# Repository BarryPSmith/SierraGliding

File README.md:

<h1 align=center>Sierra Gliding Weather</h1>

<p align=center>Low Interval Wind Station</p>

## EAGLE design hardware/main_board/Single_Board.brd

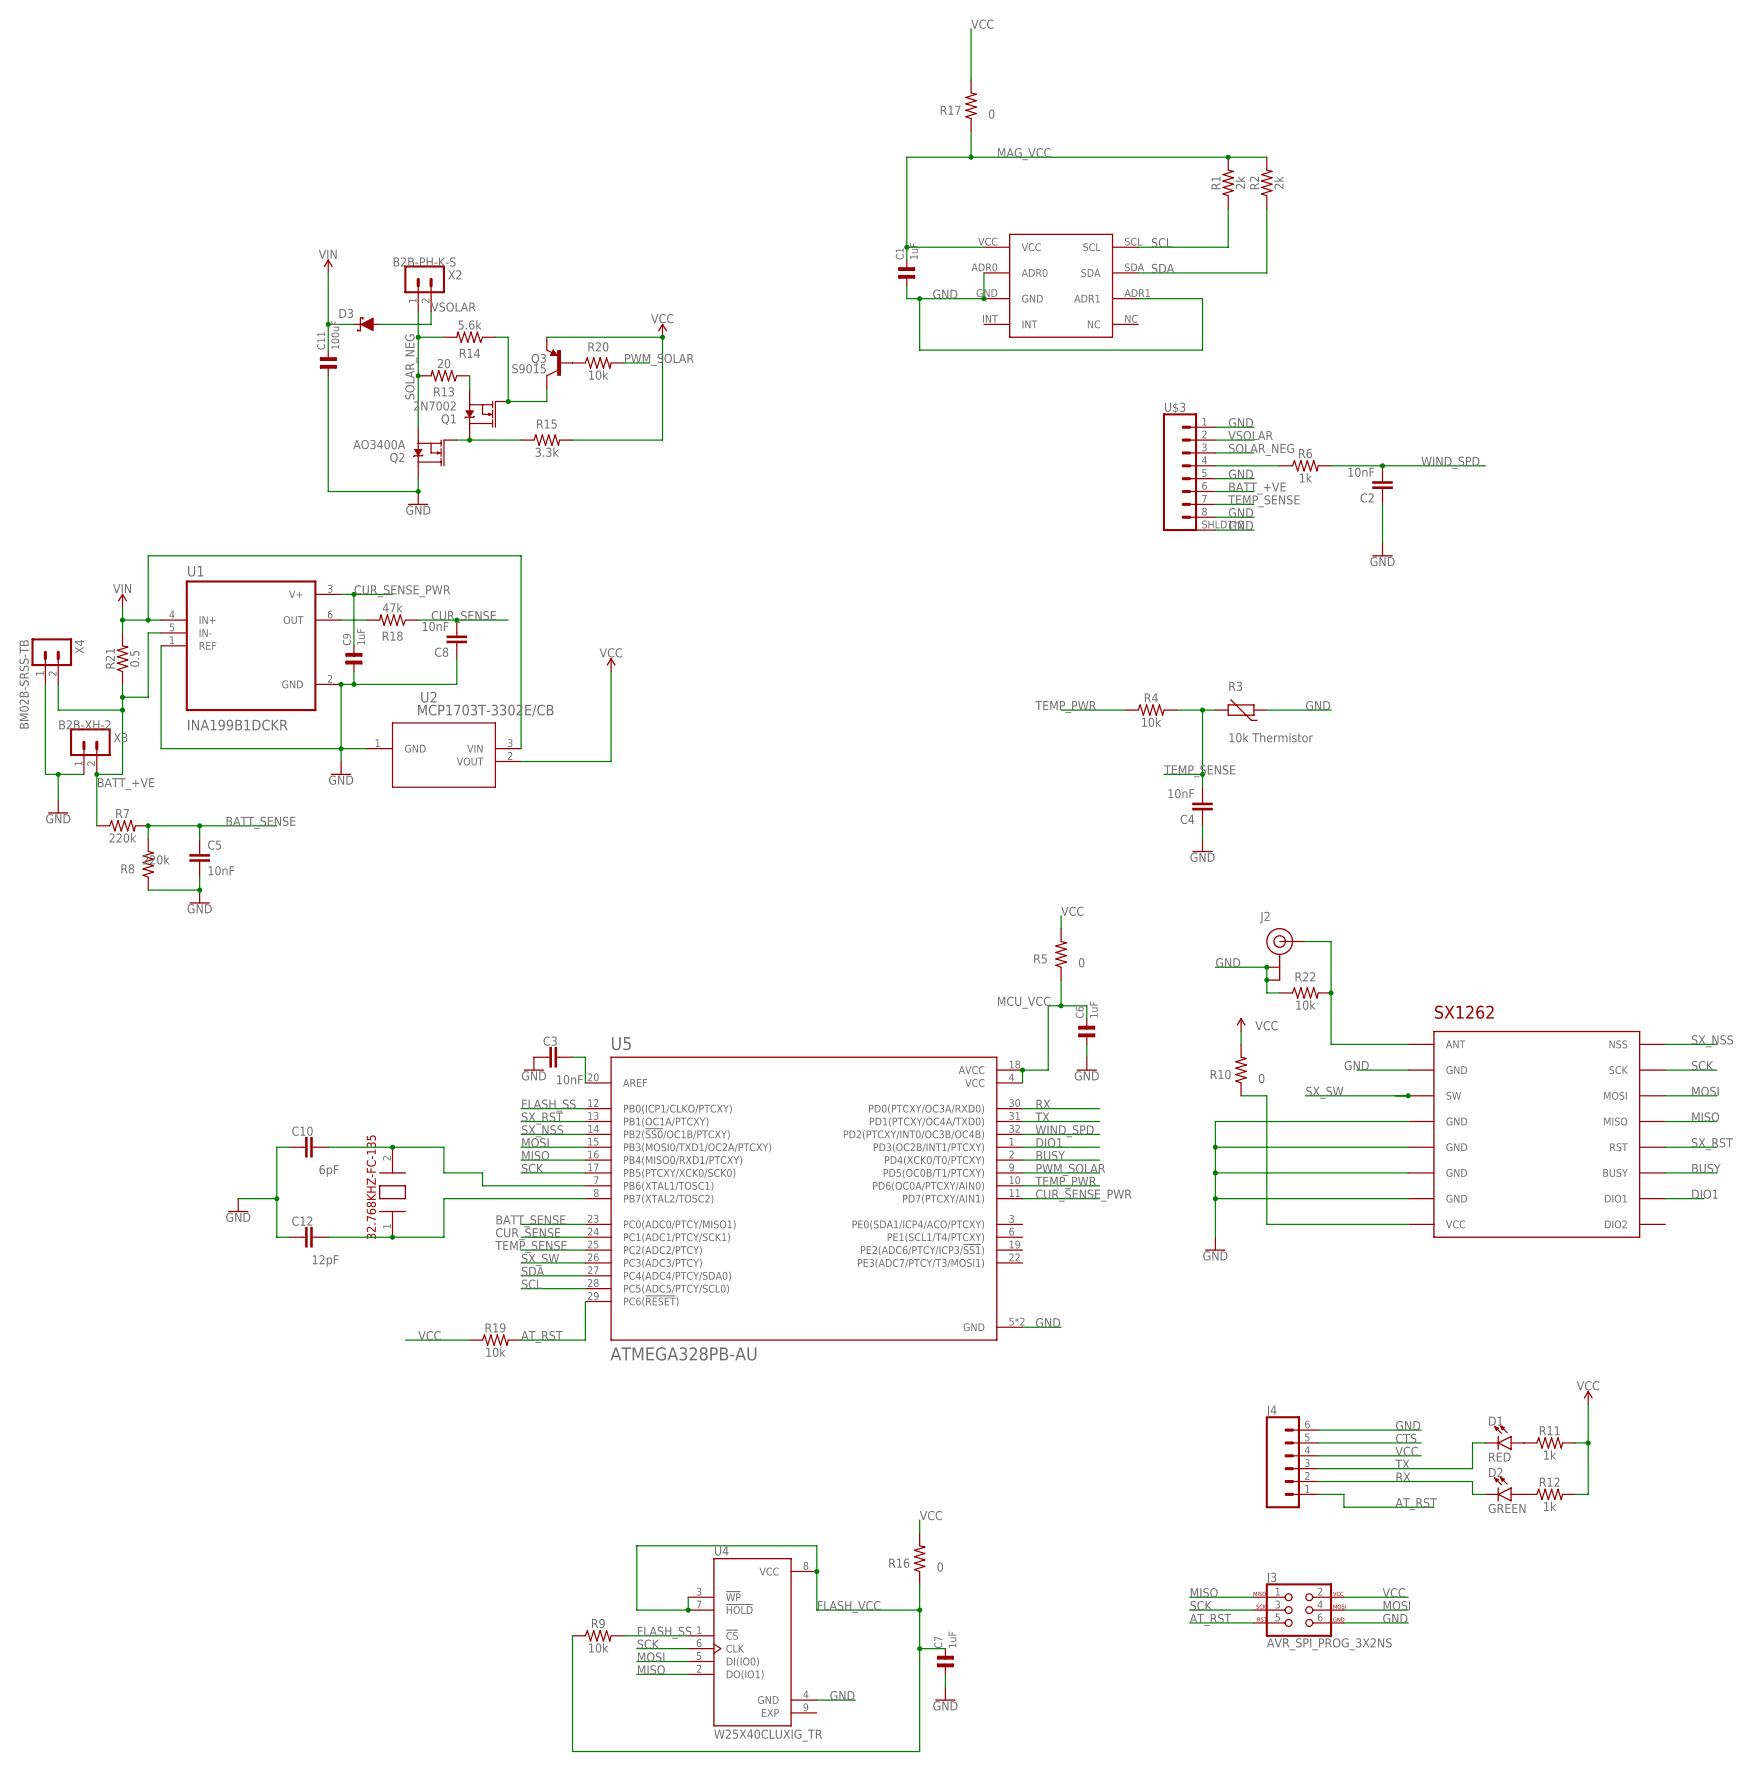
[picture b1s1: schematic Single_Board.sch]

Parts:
C1, C6, C7, C9: 1uF; 0805
C2, C3, C4, C5, C8: 10nF; 0603
C10: 6pF; 0603
C11: 100uF; 1206
C12: 12pF; 0603
D1: RED; LED-1206
D2: GREEN; LED-1206
D3: NSR0240HT1G; SOD-323
J2: U.FL
J3: AVR_SPI_PROG_3X2NS; 2X3-NS
J4: CONN_06NO_SILK_FEMALE_PTH; 1X06_NO_SILK
Q1: 2N7002; SOT23-3
Q2: AO3400A; SOT23-3
Q3: S9015; SOT23-3
R1, R2: 2k; 0805
R3: 10k Thermistor; R-5
R4, R9, R19, R20, R22: 10k; 0805
R5, R10, R16, R17: 0; 0805
R6, R11, R12: 1k; 0805
R7, R8: 220k; 0805
R13: 20; 0805
R14: 5.6k; 0805
R15: 3.3k; 0805
R18: 47k; 0805
R21: 0.5; 1206
U1: INA199B1DCKR; SOT65P210X110-6N
U2: MCP1703T-3302E/CB; SOT-23A_MC
U4: W25X40CLUXIG_TR; PSON50P300X200X60-9N
U5: ATMEGA328PB-AU; QFP80P900X900X120-32N
U$1: ALS31313; ALS31313-500
U$2: SX1262
U$3: RJSHE3380; RJHSE-3380
X1: 32.768KHZ-FC-135
X2: B2B-PH-K-S
X3: B2B-XH-2; B2B-XH-A
X4: BM02B-SRSS-TB

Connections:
ANT: J2.FEED (SIGNAL), R22.2, U$2.ANT
AT_RST: J3.5, J4.1, R19.2, U5.29 (PC6(!RESET!))
BATT_+VE: R7.1, R21.1, U1.5 (IN-), U$3.6, X3.2, X4.2
BATT_SENSE: C5.1, R7.2, R8.2, U5.23 (PC0(ADC0/PTCY/MISO1))
BUSY: U5.2 (PD4(XCK0/T0/PTCXY)), U$2.BUSY
CTS: J4.5
CUR_SENSE: C8.2, R18.1, U5.24 (PC1(ADC1/PTCY/SCK1))
CUR_SENSE_PWR: C9.2, U1.3 (V+), U5.11 (PD7(PTCXY/AIN1))
DIO1: U5.1 (PD3(OC2B/INT1/PTCXY)), U$2.DIO1
EXP: U4.9 (EXP)
FLASH_SS: R9.2, U4.1 (!CS), U5.12 (PB0(ICP1/CLKO/PTCXY))
FLASH_VCC: C7.2, R9.1, R16.1, U4.3 (!WP), U4.7 (!HOLD), U4.8 (VCC)
GND: C1.1, C2.1, C3.1, C4.1, C5.2, C6.1, C7.1, C8.1, C9.1, C10.1, C11.1, C12.1, J2.1 (GND), J2.2 (GND), J3.6, J4.6, Q2.3 (D), R3.1, R8.1, R22.1, U1.1 (REF), U1.2 (GND), U2.1 (GND), U4.4 (GND), U5.5 (GND), U5.21 (GND), U$1.ADR0, U$1.ADR1, U$1.GND, U$2.GND@1 (GND), U$2.GND@2 (GND), U$2.GND@3 (GND), U$2.GND@4 (GND), U$2.GND@5 (GND), U$3.1, U$3.5, U$3.8, U$3.SHLD1 (SHLD), U$3.SHLD2 (SHLD), X3.1, X4.1
MAG_VCC: C1.2, R1.2, R2.2, R17.1, U$1.VCC
MCU_VCC: C6.2, R5.1, U5.4 (VCC), U5.18 (AVCC)
MISO: J3.1, U4.2 (DO(IO1)), U5.16 (PB4(MISO0/RXD1/PTCXY)), U$2.MISO
MOSI: J3.4, U4.5 (DI(IO0)), U5.15 (PB3(MOSI0/TXD1/OC2A/PTCXY)), U$2.MOSI
unnamed: R10.1, U$2.VCC
unnamed: C3.2, U5.20 (AREF)
unnamed: Q1.2 (S), R13.1
unnamed: D1.A, R11.1
unnamed: R18.2, U1.6 (OUT)
unnamed: D2.A, R12.1
unnamed: C10.2, U5.7 (PB6(XTAL1/TOSC1)), X1.2 (2.XIN)
unnamed: C12.2, U5.8 (PB7(XTAL2/TOSC2)), X1.1 (1.XIN)
unnamed: Q3.1 (B), R20.1
unnamed: Q1.3 (D), Q2.1 (G), R15.1
unnamed: Q1.1 (G), Q3.3 (C), R14.1
unnamed: R6.1, U$3.4
PWM_SOLAR: R20.2, U5.9 (PD5(OC0B/T1/PTCXY))
RX: D2.C, J4.2, U5.30 (PD0(PTCXY/OC3A/RXD0))
SCK: J3.3, U4.6 (CLK), U5.17 (PB5(PTCXY/XCK0/SCK0)), U$2.SCK
SCL: R1.1, U5.28 (PC5(ADC5/PTCY/SCL0)), U$1.SCL
SDA: R2.1, U5.27 (PC4(ADC4/PTCY/SDA0)), U$1.SDA
SOLAR_NEG: Q2.2 (S), R13.2, R14.2, U$3.3, X2.1
SX_NSS: U5.14 (PB2(!SS0!/OC1B/PTCXY)), U$2.NSS
SX_RST: U5.13 (PB1(OC1A/PTCXY)), U$2.RST
SX_SW: U5.26 (PC3(ADC3/PTCY)), U$2.SW
TEMP_PWR: R4.1, U5.10 (PD6(OC0A/PTCXY/AIN0))
TEMP_SENSE: C4.2, R3.2, R4.2, U5.25 (PC2(ADC2/PTCY)), U$3.7
TX: D1.C, J4.3, U5.31 (PD1(PTCXY/OC4A/TXD0))
VCC: J3.2, J4.4, Q3.2 (E), R5.2, R10.2, R11.2, R12.2, R15.2, R16.2, R17.2, R19.1, U2.2 (VOUT)
VIN: C11.2, D3.C, R21.2, U1.4 (IN+), U2.3 (VIN)
VSOLAR: D3.A, U$3.2, X2.2
WIND_SPD: C2.2, R6.2, U5.32 (PD2(PTCXY/INT0/OC3B/OC4B))

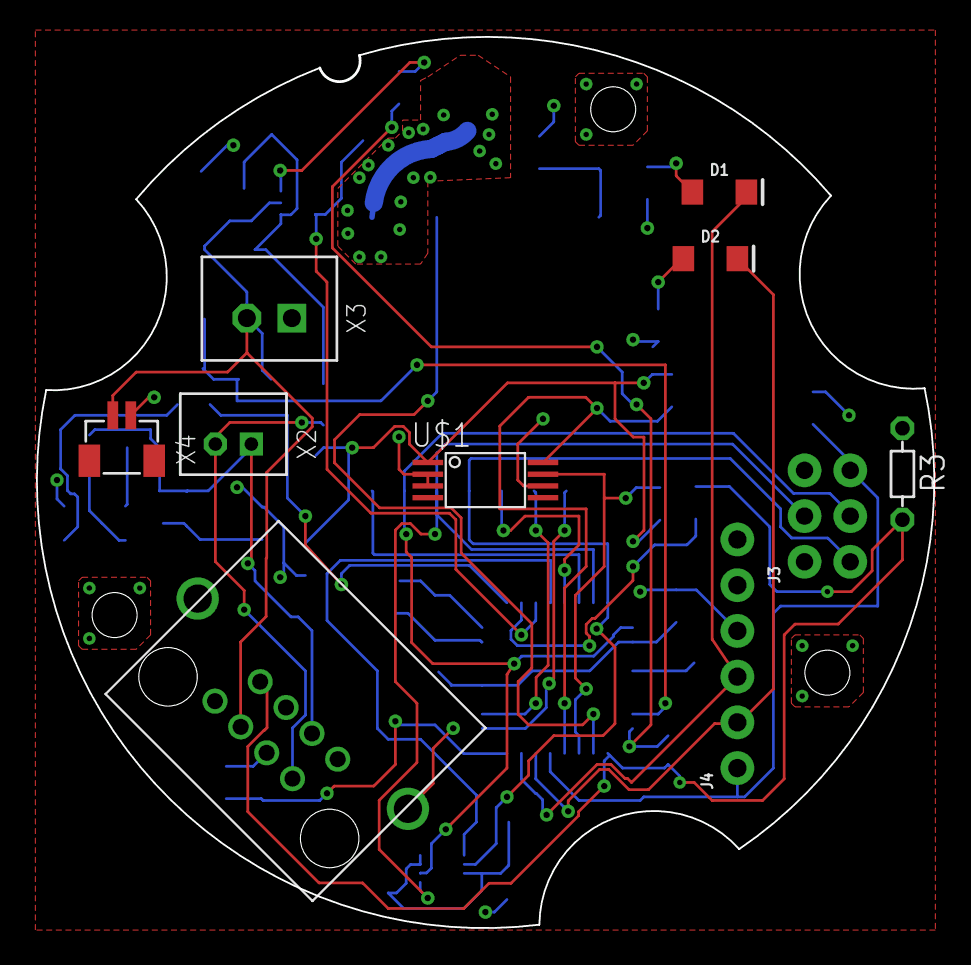
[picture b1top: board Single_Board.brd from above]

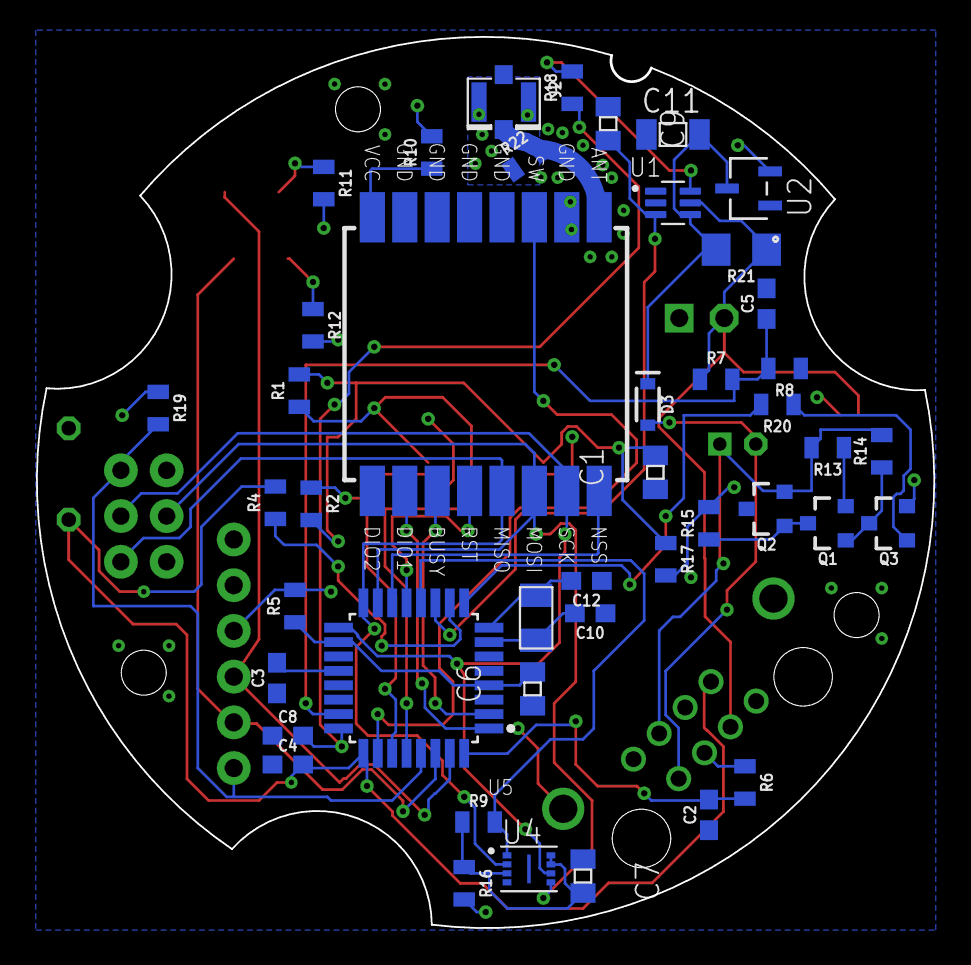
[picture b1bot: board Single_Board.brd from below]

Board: 2 copper layers, 49.8 x 49.5 mm, 54 parts (44 on the bottom side), 43 nets.

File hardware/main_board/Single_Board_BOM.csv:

Qty,Designator,Comment,Package,Device,LCSC Part #,Description
4,"R5, R10, R16, R17",0,805,RESISTOR0805,C17477,Generic Resistor Package
1,R21,0.5,1206,RESISTOR1206,C25340,Generic Resistor Package
1,D3,NSR0240HT1G,SOD-323,DIODE-SCHOTTKY,C152519,Schottky diode
1,C11,100uF,1206,C1206,C15008,Ceramic capacitor
4,"R4, R9, R19, R20",10k,805,RESISTOR0805,C17414,Generic Resistor Package
5,"C2, C3, C4, C5, C8",10nF,603,10NF-0603-50V-10%,C57112,Ceramic capacitor
3,"R6, R11, R12",1k,805,RESISTOR0805,C17513,Generic Resistor Package
4,"C1, C6, C7, C9",1uF,805,C0805,C28323,Generic Resistor Package
1,R13,20,805,RESISTOR0805,C17544,Generic Resistor Package
2,"R7, R8",220k,805,RESISTOR0805,C17556,Generic Resistor Package
1,Q1,2N7002,SOT23-3,MOSFET-NCH,C8545,N-channel MOSFETs
2,"R1, R2",2k,805,RESISTOR0805,C17604,Generic Resistor Package
1,X1,32.768KHZ-FC-135,32.768KHZ-FC-135,32.768KHZ-FC-135,C32346,RTC Crystal
1,R18,47k,805,RESISTOR0805,C17713,Generic Resistor Package
1,R14,5.6k,805,RESISTOR0805,C4382,Generic Resistor Package
1,Q2,AO3400A,SOT23-3,MOSFET-NCH,C20917,N-channel MOSFETs
1,U5,ATMEGA328P-AU,QFP80P900X900X120-32N,ATMEGA328P-AU,C14877,ATmega Series 20 MHz 32 KB Flash 2 KB SRAM 8-Bit Microcontroller - TQFP-32
1,U1,INA199B1DCKR,SOT65P210X110-6N,INA199B1DCKR,C398920,Current sense amplifier
1,U2,MCP1703T-3302E/CB,SOT-23A_MC,MCP1703T-3302E/CB,C53352,3.3V low power linear regulator
1,U4,W25X40CLUXIG_TR,PSON50P300X200X60-9N,W25X40CLUXIG_TR,C401661,4Mb SPI flash
1,C10,6pF,603,C0603,C37474,Ceramic capacitor
1,C12,12pF,603,C0603,C38523,Ceramic capacitor
1,R15,3.3k,805,RESISTOR0805,C26010,Generic Resistor Package
1,Q3,S9015,SOT23-3,TRANS_PNP,C2149,PNP transistor

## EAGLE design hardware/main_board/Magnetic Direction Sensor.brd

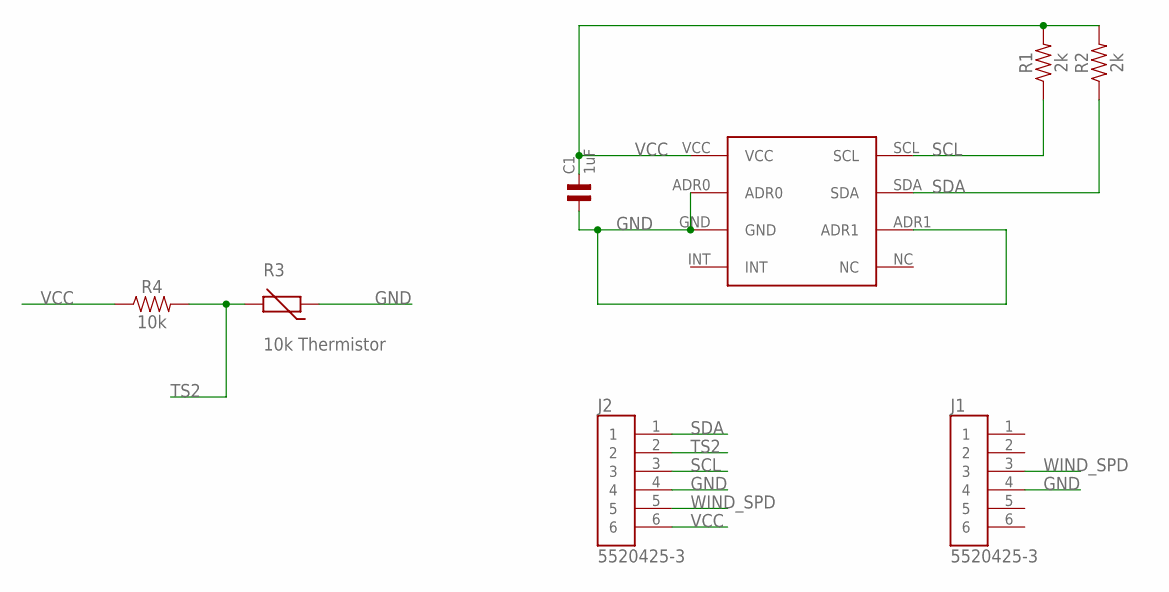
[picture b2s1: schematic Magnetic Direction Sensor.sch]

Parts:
C1: 1uF; 0805
J1, J2: 5520425-3; TE_5520425-3
R1, R2: 2k; 0805
R3: 10k Thermistor; R-5
R4: 10k; 0805
U$1: ALS31313; ALS31313-500

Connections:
GND: C1.1, J1.4, J2.4, R3.1, U$1.ADR0, U$1.ADR1, U$1.GND
SCL: J2.3, R1.1, U$1.SCL
SDA: J2.1, R2.1, U$1.SDA
TS2: J2.2, R3.2, R4.2
VCC: C1.2, J2.6, R1.2, R2.2, R4.1, U$1.VCC
WIND_SPD: J1.3, J2.5

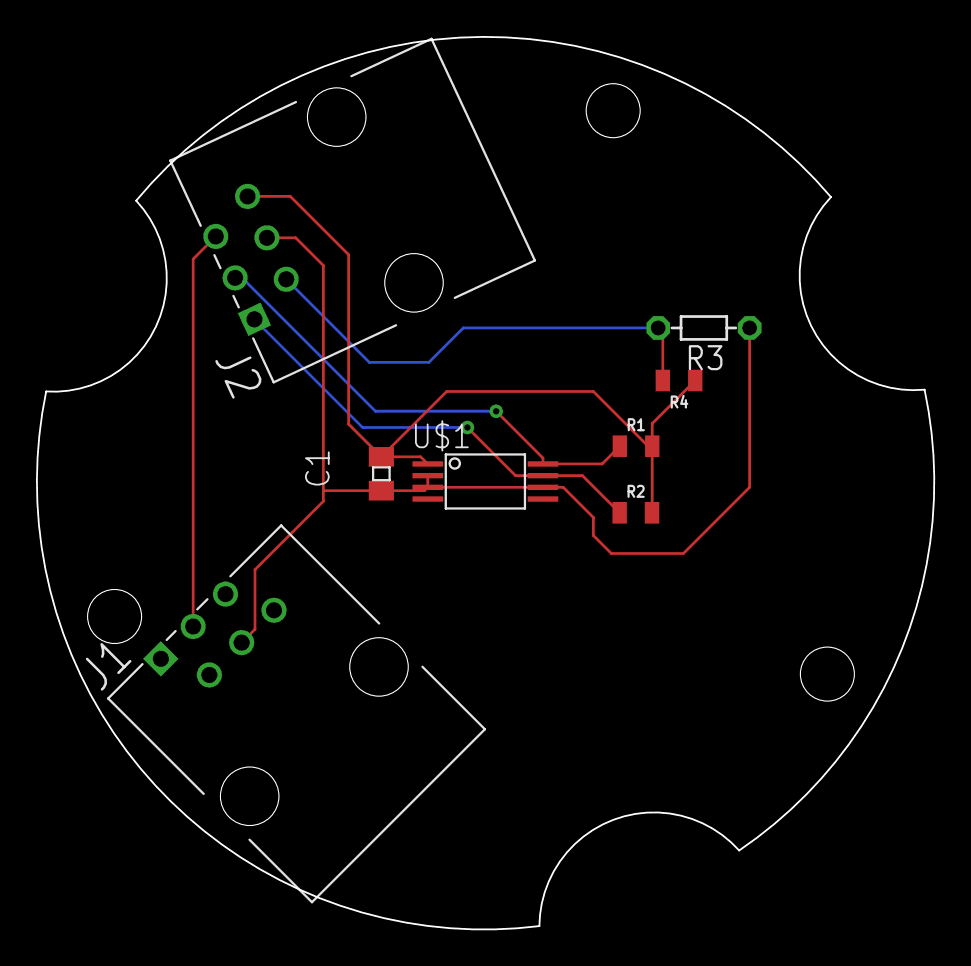
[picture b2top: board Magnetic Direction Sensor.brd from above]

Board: 2 copper layers, 49.9 x 49.6 mm, 8 parts (0 on the bottom side), 6 nets.

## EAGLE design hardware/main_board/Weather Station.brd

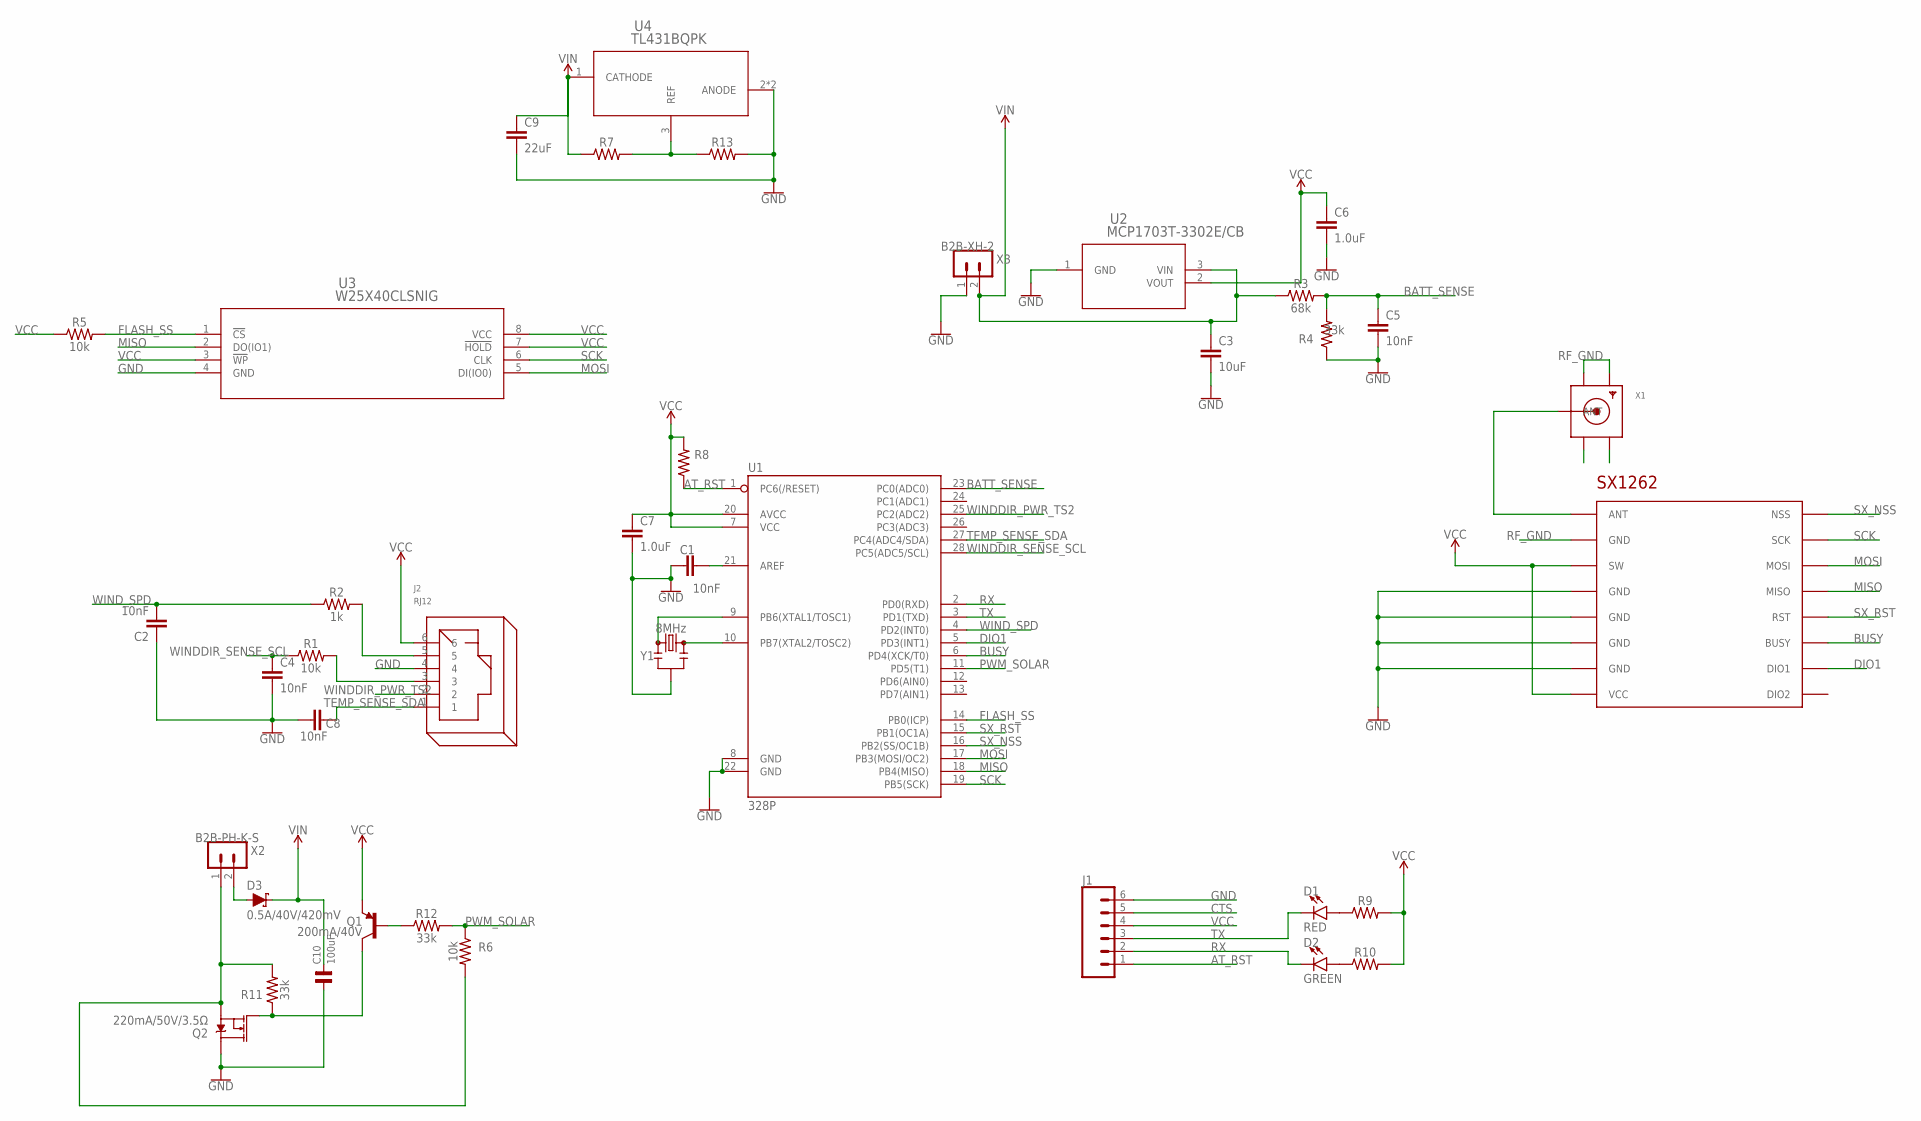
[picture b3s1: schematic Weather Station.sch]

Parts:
C1, C2, C4, C5, C8: 10nF; 0603
C3: 10uF; 0603
C6: 1.0uF; 0603
C7: 1.0uF; 0805
C9: 22uF; 0805
C10: 100uF; 1206
D1: RED; LED-1206
D2: GREEN; LED-1206
D3: 0.5A/40V/420mV; SOD-323
J1: CONN_06NO_SILK_FEMALE_PTH; 1X06_NO_SILK
J2: RJ12
Q1: 200mA/40V; SOT23-3
Q2: 220mA/50V/3.5Ω; SOT23-3
R1, R5, R6: 10k; 0805
R2: 1k; 0805
R3: 68k; 0805
R4, R11, R12: 33k; 0805
R7, R8, R9, R10, R13: 0805
U1: 328P; DIP28
U2: MCP1703T-3302E/CB; SOT-23A_MC
U3: W25X40CLSNIG; WIN_SN-8
U4: TL431BQPK; PK3
U$1: SX1262
X1: SMACONNECTOR_EDGE_UFL; SMA_EDGELAUNCH_UFL
X2: B2B-PH-K-S
X3: B2B-XH-2; B2B-XH-A
Y1: 8MHz; RESONATOR-SMD-3.2X1.3

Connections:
ANT: U$1.ANT, X1.P (ANT)
AT_RST: J1.1, R8.1, U1.1 (PC6(/RESET))
BATT_SENSE: C5.1, R3.2, R4.2, U1.23 (PC0(ADC0))
BUSY: U1.6 (PD4(XCK/T0)), U$1.BUSY
CTS: J1.5
DIO1: U1.5 (PD3(INT1)), U$1.DIO1
FLASH_SS: R5.2, U1.14 (PB0(ICP)), U3.1 (!CS)
GND: C1.1, C2.1, C3.2, C4.2, C5.2, C6.2, C7.2, C8.2, C9.2, C10.1, J1.6, J2.4, Q2.3 (D), R4.1, R13.2, U1.8 (GND), U1.22 (GND), U2.1 (GND), U3.4 (GND), U4.2 (ANODE), U4.A2 (ANODE), U$1.GND@2 (GND), U$1.GND@3 (GND), U$1.GND@4 (GND), U$1.GND@5 (GND), X3.1, Y1.2
MISO: U1.18 (PB4(MISO)), U3.2 (DO(IO1)), U$1.MISO
MOSI: U1.17 (PB3(MOSI/OC2)), U3.5 (DI(IO0)), U$1.MOSI
unnamed: R7.2, R13.1, U4.3 (REF)
unnamed: J2.5, R2.2
unnamed: D1.A, R9.1
unnamed: D2.A, R10.1
unnamed: J2.3, R1.2
unnamed: C1.2, U1.21 (AREF)
unnamed: Q2.2 (S), R6.2, R11.2, X2.1
unnamed: U1.9 (PB6(XTAL1/TOSC1)), Y1.1
unnamed: U1.10 (PB7(XTAL2/TOSC2)), Y1.3
unnamed: Q1.3 (C), Q2.1 (G), R11.1
unnamed: Q1.1 (B), R12.1
unnamed: D3.A, X2.2
PWM_SOLAR: R6.1, R12.2, U1.11 (PD5(T1))
RF_GND: U$1.GND@1 (GND), X1.GND@1 (GND1), X1.GND@2 (GND2)
RX: D2.C, J1.2, U1.2 (PD0(RXD))
SCK: U1.19 (PB5(SCK)), U3.6 (CLK), U$1.SCK
SX_NSS: U1.16 (PB2(SS/OC1B)), U$1.NSS
SX_RST: U1.15 (PB1(OC1A)), U$1.RST
TEMP_SENSE_SDA: C8.1, J2.1, U1.27 (PC4(ADC4/SDA))
TX: D1.C, J1.3, U1.3 (PD1(TXD))
VCC: C6.1, C7.1, J1.4, J2.6, Q1.2 (E), R5.1, R8.2, R9.2, R10.2, U1.7 (VCC), U1.20 (AVCC), U2.2 (VOUT), U3.3 (!WP), U3.7 (!HOLD), U3.8 (VCC), U$1.SW, U$1.VCC
VIN: C3.1, C9.1, C10.2, D3.C, R3.1, R7.1, U2.3 (VIN), U4.1 (CATHODE), X3.2
WINDDIR_PWR_TS2: J2.2, U1.25 (PC2(ADC2))
WINDDIR_SENSE_SCL: C4.1, R1.1, U1.28 (PC5(ADC5/SCL))
WIND_SPD: C2.2, R2.1, U1.4 (PD2(INT0))

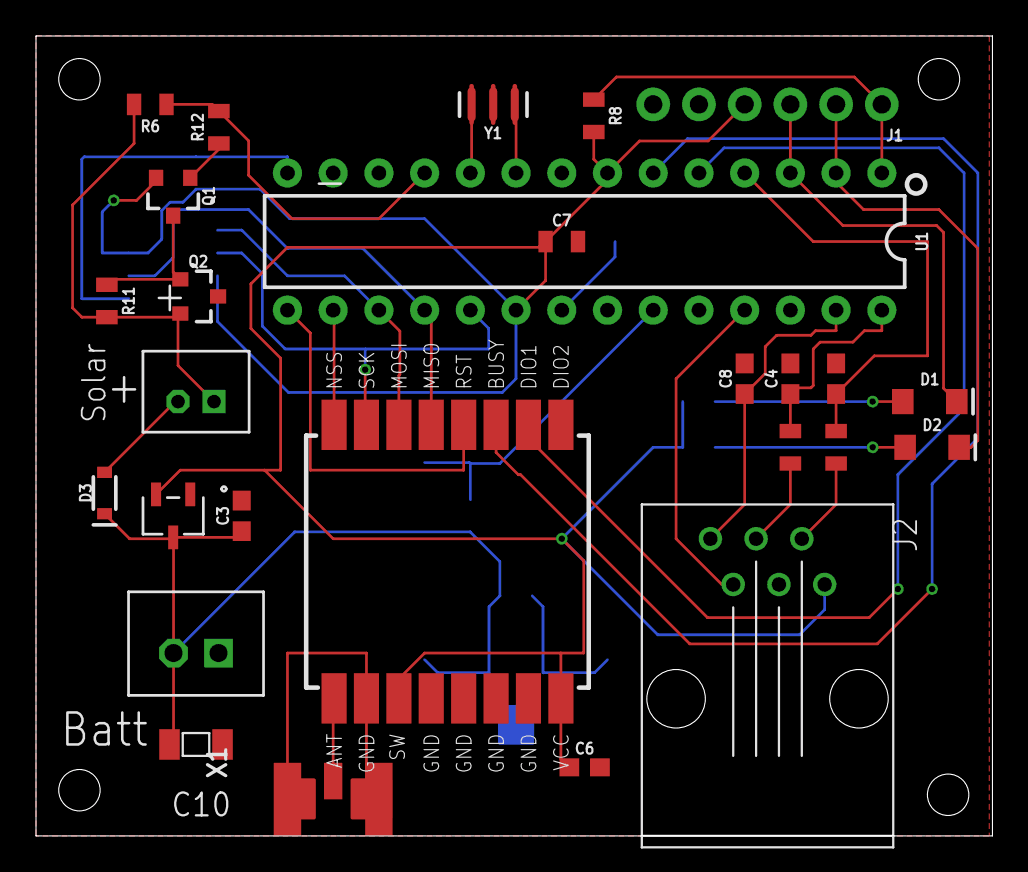
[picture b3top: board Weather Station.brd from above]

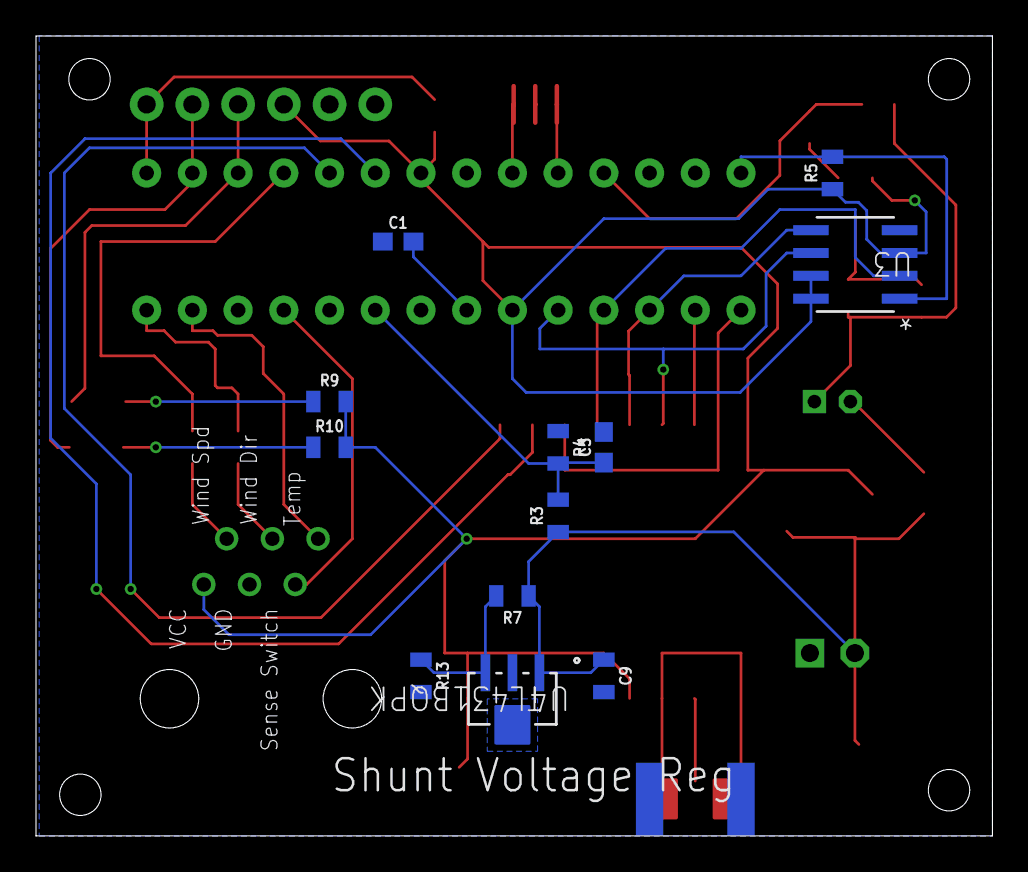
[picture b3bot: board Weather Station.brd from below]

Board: 2 copper layers, 53.1 x 44.4 mm, 39 parts (12 on the bottom side), 34 nets.

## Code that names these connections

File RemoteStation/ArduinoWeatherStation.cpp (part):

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#if SX_SWITCH != A3
  pinMode(A3, INPUT_PULLUP);
#endif
#if TEMP_PWR_PIN != 6
  pinMode(6, INPUT_PULLUP);
#endif
#if CURRENT_SENSE_PWR != 7
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void enterStasis()
{
  // If we don't have a wind speed pin, we can't enter stasis
#ifdef WIND_SPD_PIN
  batteryMode = BatteryMode::Stasis;
  WeatherProcessing::enterDeepSleep();
  sleepRadio();
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  static_assert(LED_ON == LOW);
  static_assert(LED_OFF == HIGH);
  auto delay2 = delay_ms / 4;
  PORTD &= ~(_BV(PD0) | _BV(PD1));
  //digitalWrite(LED_PIN0, LED_ON);
  //digitalWrite(LED_PIN1, LED_ON);
  delay(delay2);
  PORTD |= _BV(PD1);//digitalWrite(LED_PIN1, LED_OFF);
  delay(delay2);
  PORTD &= ~_BV(PD1); //digitalWrite(LED_PIN1, LED_ON);
  delay(delay2);
  PORTD |= _BV(PD1); //digitalWrite(LED_PIN1, LED_OFF);
  delay(delay2);
  //Shorten it to 11 bits (=-1024 to + 1023)
  for (byte i = 0; i < 11; i++)
  {
    if (i & 1)
      PORTD |= _BV(PD0); //OFF for i = 1, 3, 5, 7, 9, 11
    else
      PORTD &= ~_BV(PD0); //ON for i = 0, 2, 4, 8, 10
    //digitalWrite(LED_PIN0, (i & 1) ? LED_OFF : LED_ON);
    if (errorCode & 1)
      PORTD &= ~_BV(PD1);
    else
      PORTD |= _BV(PD1);
    //digitalWrite(LED_PIN1, (errorCode & 1) ? LED_ON : LED_OFF);
    errorCode = errorCode >> 1;
    delay(delay_ms);
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  //digitalWrite(LED_PIN0, LED_OFF);
  //digitalWrite(LED_PIN1, errorCode & (0x800 >> 11) ? LED_ON : LED_OFF);
  if (errorCode & (0x800 >> 11))
    PORTD &= ~_BV(PD1);
  else
    PORTD |= _BV(PD1);
  PORTD |= _BV(PD0);
  delay(delay_ms);
  signalOff();
#endif
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
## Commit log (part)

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2019-10-06 Allow switching between durations
2019-10-06 Add Error Handling
2019-10-06 Add windspeed legend checks
2019-10-06 Add clearfix
2019-10-06 Add actual lat/lngs
2019-10-07 Add sample URL param validity checks
2019-10-08 Fix README geojson
2019-10-08 Made dotNet_Receiver configurable. Added wind direction offset to database schema
2019-10-08 Separated wind and battery charts. Legend work.
2019-10-09 Ignore all sqlite files
2019-10-09 Chart time axes appear. Needed min and max on annotations.
2019-10-09 Made graphs take up all available space through use of custom grid styles.
2019-10-09 Fixed a bug in legend parsing while fetching stations. Unimportant since it's not used
2019-10-10 Secure websockets
2019-10-10 Migrated receiver to dotNet core 3.0 so it can run on Linux
2019-10-13 Receiver improvements
2019-10-17 Rearranged hardware folder. Adding more hardware documentation
2019-10-20 Added ability to pan graphs using click and drag. Things are strange. Why do I now need to require('Annotations')?
2019-10-20 Windspeed scaling after panning and loading new data
2019-11-05 Added an optional status message to stations
2019-11-14 Weather station LoRa work
2019-11-15 Work on the arduino software. Also an arduino Kiss Modem.
2019-11-16 Made everything work of Timer1 millis. Added debounce to windspeed logic.
2019-11-19 A bunch of changes. Most significantly, made the modem use DIO2 as a RF switch. Tried to add Moteino support with the RF96 module. No luck yet. Some other stuff
2019-11-20 Clawing memory back using F(...)
2019-11-28 Changed to Timer2 so we can put the ATMega to sleep
2019-12-10 Big changes all over.
2019-12-11 Customisable battery range. Switched erratic time behaviour when switching between battery and wind.
2019-12-24 Fixed a couple bugs in millis and micros implementations
2020-01-05 Changed to gnu make instead of NMAKE. Various other work too Untested.
2020-01-12 Added some power saving stuff, disabled for now. This image should be run at Flynns for a while
2020-01-25 Added temperature sense. MCU sleeps more.
2020-01-28 Added wind calibration. Started using namespaces. Added indicator LEDs
2020-01-28 Weather station + receiver stuff.
2020-02-03 Website work
2020-02-03 More Mt Tom fixes.
2020-02-10 Fixed a bug in weather relay. Made receiver more resilient to this bug.
2020-02-13 Reworked site to use webpack. Reworked server sampling to do it in SQLite for improved performance.
2020-02-14 Added capability to change wind direction graph centre.
2020-02-17 Remote Programming implemented (not connected). Tweaked relay logic.
2020-02-25 Webserver bugfix
2020-02-25 Minor code cleanup
2020-02-27 Changed site to 15 minute default duration
2020-03-03 Fixed legends not being visible until chart got new data
2020-03-09 Added transparency to wind direction chart
2020-03-14 Fix messed up arrow indicator on firefox
2020-03-14 Fix firefox
2020-03-14 Alignment
2020-03-21 Random ID assigment limited to [1,127] because IDs can't start with 0x80
2020-04-03 Clawed back some space
2020-04-06 Bump minimist from 1.2.0 to 1.2.3 in /web
    Bumps [minimist](https://github.com/substack/minimist) from 1.2.0 to 1.2.3.
    - [Release notes](https://github.com/substack/minimist/releases)
    - [Commits](https://github.com/substack/minimist/compare/1.2.0...1.2.3)
2020-04-09 ALS Wind direction bug fixes. Added ability to chain receivers using UDP. QueryVolatileResponse bugfix.
2020-04-14 Added more power saving options: Disable continuous receive & deep sleep, clock divider Receiver: Ability to handle extra bytes on weather packets
2020-05-01 Added magnetic direction sensor board
2020-05-03 Added windy poster.
2020-05-12 Station backward compatibility fixes. Site: Can now request hidden stations, made temperature chart sizeable on click.
2020-05-19 Added mechanism to write ALS eeprom
2020-05-23 More bugfixes with CSMA queueing Added GUIDs to UDP packets to avoid repeated processing
2020-05-31 Added docs folder
2020-05-31 Set theme jekyll-theme-slate
2020-06-24 Documentation work
2020-07-18 Bump lodash from 4.17.14 to 4.17.19 in /web/site
    Bumps [lodash](https://github.com/lodash/lodash) from 4.17.14 to 4.17.19.
    - [Release notes](https://github.com/lodash/lodash/releases)
    - [Commits](https://github.com/lodash/lodash/compare/4.17.14...4.17.19)
2020-08-08 Improved chart time axes, aligned detail charts with wind chart.
2020-08-31 Big changes: 2.3, flash message storage, permanent time
2020-09-03 More station improvements
2020-09-04 Added command guards. Saves stack trace on reboot.
2020-09-05 Programmer fixes with new extra CRC checks
2020-09-19 pany fix
2020-11-17 Added ability to jump times. Improved receiver command help
2020-12-08 Added daylight indicators
2020-12-08 Bump dot-prop from 4.2.0 to 4.2.1 in /web/site
    Bumps [dot-prop](https://github.com/sindresorhus/dot-prop) from 4.2.0 to 4.2.1.
    - [Release notes](https://github.com/sindresorhus/dot-prop/releases)
    - [Commits](https://github.com/sindresorhus/dot-prop/compare/v4.2.0...v4.2.1)
2021-01-01 Station improvements. Multi-subpacket handling in receiver. Out of order packets in site datamanager.
2021-02-01 Reduced web server load through low resolution tables
2021-02-02 Further sig fig reductions
2021-02-14 Saving program space: Removed many icalls Switched to home-brew synchronous two wire
2021-03-17 Removed remote switch control. Debug parameters changed.
2021-03-23 Found a problem where the solar PWM can latch closed. Temporary fix is to set an appropriate startup value that doesn't close it.
2021-04-04 Added old centroid file purely for history
2021-04-30 Bump ssri from 6.0.1 to 6.0.2 in /web/site
    Bumps [ssri](https://github.com/npm/ssri) from 6.0.1 to 6.0.2.
    - [Release notes](https://github.com/npm/ssri/releases)
    - [Changelog](https://github.com/npm/ssri/blob/v6.0.2/CHANGELOG.md)
    - [Commits](https://github.com/npm/ssri/compare/v6.0.1...v6.0.2)
2021-05-05 Added station groups
2021-05-10 Bump lodash from 4.17.20 to 4.17.21 in /web
    Bumps [lodash](https://github.com/lodash/lodash) from 4.17.20 to 4.17.21.
    - [Release notes](https://github.com/lodash/lodash/releases)
    - [Commits](https://github.com/lodash/lodash/compare/4.17.20...4.17.21)
2021-05-29 Bump ws from 7.1.2 to 7.4.6 in /web
    Bumps [ws](https://github.com/websockets/ws) from 7.1.2 to 7.4.6.
    - [Release notes](https://github.com/websockets/ws/releases)
    - [Commits](https://github.com/websockets/ws/compare/7.1.2...7.4.6)
2021-08-11 Bump path-parse from 1.0.6 to 1.0.7 in /web/site
    Bumps [path-parse](https://github.com/jbgutierrez/path-parse) from 1.0.6 to 1.0.7.
    - [Release notes](https://github.com/jbgutierrez/path-parse/releases)
    - [Commits](https://github.com/jbgutierrez/path-parse/commits/v1.0.7)
    ---
    updated-dependencies:
    - dependency-name: path-parse
2021-09-20 Bump color-string from 1.5.3 to 1.6.0 in /web/site
    Bumps [color-string](https://github.com/Qix-/color-string) from 1.5.3 to 1.6.0.
    - [Release notes](https://github.com/Qix-/color-string/releases)
    - [Changelog](https://github.com/Qix-/color-string/blob/master/CHANGELOG.md)
    - [Commits](https://github.com/Qix-/color-string/commits/1.6.0)
    ---
    updated-dependencies:
2021-11-01 Modem automatically restarts the radio if it doesn't receive a message in 6 seconds Stations select default frequency and bandwidth if frequency is out of range Fixed a bug with weather relay overflo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
2021-12-07 Added ability to change inbound preamble length
2021-12-08 Fixed a uninitalised pointer and threading bug introduced in previous commit.ISP programming now preserves EEPROM
2021-12-08 Re-enabled modem watchdog Inbound preamble length reset to 8 in low power modes Improved receiver logging
2021-12-11 Test function in receiver Debugging to try figure out what's going on with relays sometimes sending invalid data Misc formatting & display
2021-12-11 Improved gust calculation to use 4 rotations rather than 1. Webserver refuses packets with inverted windspeed / gust.
2021-12-14 The eternal struggle with memory. Fixed a bug where the current read packet could get corrupted when a packet is sent. Fixed a problem with buffer overrun when recording messages for relay Improved r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
2021-12-15 Got rid of npm security warnings, with some major version upgrades in there to boot.
2021-12-16 Add HTTPError
2021-12-16 npm audit really doesn't like sqlite5
2021-12-31 Added PWM to current display
2022-01-01 Receiver ability to handle RSSI/SNR on recently seen station list
2022-01-03 Limited preamble lengths to stop accidental bricking of stations. dotNetReceiver now configurable for stations with different version (instead of hardcoded.
2022-01-08 Fixed assignment to a constant variable error.
2022-01-21 Sunrise/sunset calcs now use actual station locations
2022-01-23 Button font size
2022-01-24 Re-enabled /all
2022-03-24 Bump minimist from 1.2.5 to 1.2.6 in /web/site
    Bumps [minimist](https://github.com/substack/minimist) from 1.2.5 to 1.2.6.
    - [Release notes](https://github.com/substack/minimist/releases)
    - [Commits](https://github.com/substack/minimist/compare/1.2.5...1.2.6)
    ---
    updated-dependencies:
    - dependency-name: minimist
2022-06-22 Bump Newtonsoft.Json in /dotNet_Receiver/dotNet_Receiver
    Bumps [Newtonsoft.Json](https://github.com/JamesNK/Newtonsoft.Json) from 12.0.3-beta2 to 13.0.1.
    - [Release notes](https://github.com/JamesNK/Newtonsoft.Json/releases)
    - [Commits](https://github.com/JamesNK/Newtonsoft.Json/commits/13.0.1)
    ---
    updated-dependencies:
    - dependency-name: Newtonsoft.Json
2022-11-13 Bump loader-utils from 1.4.0 to 1.4.2 in /web/site
    Bumps [loader-utils](https://github.com/webpack/loader-utils) from 1.4.0 to 1.4.2.
    - [Release notes](https://github.com/webpack/loader-utils/releases)
    - [Changelog](https://github.com/webpack/loader-utils/blob/v1.4.2/CHANGELOG.md)
    - [Commits](https://github.com/webpack/loader-utils/compare/v1.4.0...v1.4.2)
    ---
    updated-dependencies:
2022-12-08 Bump Newtonsoft.Json from 12.0.3 to 13.0.2 in /WindyPoster
    Bumps [Newtonsoft.Json](https://github.com/JamesNK/Newtonsoft.Json) from 12.0.3 to 13.0.2.
    - [Release notes](https://github.com/JamesNK/Newtonsoft.Json/releases)
    - [Commits](https://github.com/JamesNK/Newtonsoft.Json/compare/12.0.3...13.0.2)
    ---
    updated-dependencies:
    - dependency-name: Newtonsoft.Json
2023-01-07 Bump json5 from 1.0.1 to 1.0.2 in /web/site
    Bumps [json5](https://github.com/json5/json5) from 1.0.1 to 1.0.2.
    - [Release notes](https://github.com/json5/json5/releases)
    - [Changelog](https://github.com/json5/json5/blob/main/CHANGELOG.md)
    - [Commits](https://github.com/json5/json5/compare/v1.0.1...v1.0.2)
    ---
    updated-dependencies:
2023-05-04 Receiver stuff
2023-05-04 Fix lints
2023-08-02 Timestamps for averaged data are now properly at the end of their sample period
2023-12-09 Removed old component list
2025-05-01 Added recommendation to switch to maps for approach info
2026-02-03 Updated dotnet receiver to deal with new packets from WS80
2026-02-04 Fixed a few bugs in triggers from previous commit
2026-02-05 Turned out I don't have any rev3 boards, so the new station will be on Rev2
2026-03-02 Added support for dual weather. Improved behaviour when WS80 fails.
2026-03-14 Changed WS80 Rx Parameters
2026-05-28 Remote commands now working, no UI
2026-05-29 It's under the doormat.

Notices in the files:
parts and their libraries:
SparkFun-Resistors: Licensing: Creative Commons ShareAlike 4.0 International - https://creativecommons.org/licenses/by-sa/4.0
